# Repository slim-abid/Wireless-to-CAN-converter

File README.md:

# **Wireless to CAN converter**

Heracles is a qualified board for Automotive Applications.
The board was designed by KiCad.
It introduces the convertion between wireless connection (Bluetooth,BLE,WIFI) and CAN with the following features:

 - [ ] introduces a jtag debugging interface.
 
 - [ ] can be configured and managed by the integrated USB interface.
 
 - [ ] uses 3.8 to 38 V dc alimentation with very low drop down voltage
       values and very low power consumption .
 - [ ] ESP32­WROOM­32 running at 40Mhz to 160MHz.
 
 - [ ] A USB to UART converter.
 
 - [ ] USB type B port.
 
 - [ ] low-power co-processor that can be used instead of the CPU to
       save power while performing tasks that do not require much
       computing power, such as monitoring of peripherals.
       
 - [ ] Wireless connectivity: WI-FI (802.11 b/g/n ,802.11n up to 150
       Mbps), Bluetooth v4.2 and BLE.

## Schematic:

## PCB Routing

*All this capabilities are just in 6.65cmx5.35cm board.*

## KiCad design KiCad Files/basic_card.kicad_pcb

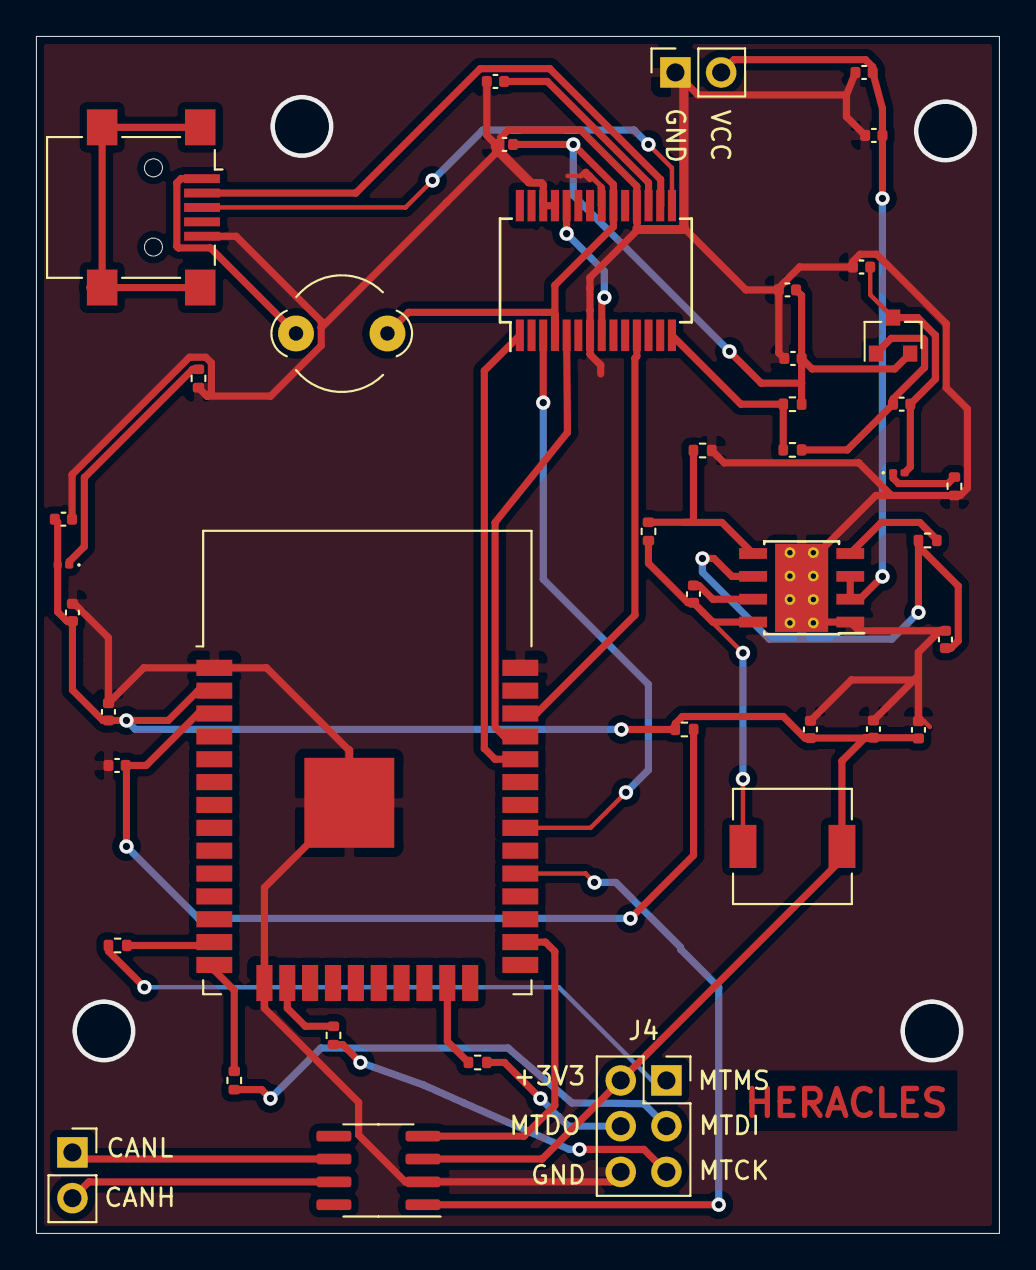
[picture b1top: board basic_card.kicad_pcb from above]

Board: 2 copper layers, 53.5 x 66.5 mm, 42 parts (0 on the bottom side), 35 nets.

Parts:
C1, C16: 10uF; C_0402_1005Metric
C2: 220nF; C_0402_1005Metric
C3: 10nF; C_0402_1005Metric
C4: C; C_0402_1005Metric
C5, C6, C8: 100nF; C_0402_1005Metric
C7: 4.7uF; C_0402_1005Metric
C9, C10, C11, C12: 22uF; C_0402_1005Metric
C13, C14, C17: 0.1uF; C_0402_1005Metric
C15: 1uF; C_0402_1005Metric
D1, D2: LED; LED_0201_0603Metric
FB1: Ferrite_Bead; LairdTech_28C0236-0JW-10
J1: USB_B_Mini; USB_Mini-B_Lumberg_2486_01_Horizontal
J2, J3: Screw_Terminal_01x02; PinSocket_1x02_P2.54mm_Vertical
J4: Conn_02x03_Odd_Even; PinSocket_2x03_P2.54mm_Vertical
L1: 6.8uH; L_6.3x6.3_H3
Q1: IRLML6402; SOT-23
R1: R; R_0402_1005Metric
R2: 100k; R_0402_1005Metric
R3: 43.2k; R_0402_1005Metric
R4, R9, R10: 1k; R_0402_1005Metric
R5, R6, R7, R11: 100; R_0402_1005Metric
R8, R12: 10k; R_0402_1005Metric
U1: SN65HVD232; SOIC-8_3.9x4.9mm_P1.27mm
U2: LMR33630ADDA; Texas_HSOP-8-1EP_3.9x4.9mm_P1.27mm_ThermalVias
U3: FT232RL; SSOP-28_5.3x10.2mm_P0.65mm
U4: ESP32-WROOM-32

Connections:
+3V3: C9.1, C10.1, C11.1, C12.1, C16.1, C17.1, D1.2, J4.2, L1.1, R12.1, U1.3, U4.2
+12V: C1.1, C2.1, J2.2, U2.2, U2.3
CAN_RXD: U1.4, U4.26
CAN_TXD: U1.1, U4.29
GND: C1.2, C2.2, C3.2, C4.2, C5.1, C6.1, C7.1, C9.2, C10.2, C11.2, C12.2, C14.2, C15.2, C16.2, C17.2, J1.5, J2.1, J4.6, R3.2, R4.2, R10.2, U1.2, U2.1, U2.9, U3.7, U3.18, U3.21, U3.25, U3.26, U4.1, U4.15, U4.38, U4.39
IO19: U3.3, U4.31
IO22: U3.11, U4.36
MTCK: R7.2, U4.16
MTDI: R6.2, U4.14
MTDO: R11.1, U4.23
MTMS: R5.2, U4.13
unnamed: C3.1, C6.2, C7.2, FB1.1, Q1.2, R8.1, U3.4, U3.20
unnamed: C4.1, R1.1, U2.6
unnamed: C5.2, U3.17
unnamed: C8.1, L1.2, R2.1, U2.8
unnamed: C8.2, U2.7
unnamed: C13.1, C14.1, D2.2, Q1.3
unnamed: C13.2, Q1.1, R9.1
unnamed: C15.1, R12.2, U4.3
unnamed: D1.1, R4.1
unnamed: D2.1, R10.1
unnamed: FB1.2, J1.1
unnamed: J1.2, U3.16
unnamed: J1.3, U3.15
unnamed: J3.1, U1.6
unnamed: J3.2, U1.7
unnamed: J4.1, R5.1
unnamed: J4.3, R6.1
unnamed: J4.4, R11.2
unnamed: J4.5, R7.1
unnamed: R2.2, R3.1, U2.5
unnamed: R8.2, R9.2, U3.14
PG: R1.2, U2.4
RX-ESP: U3.1, U4.34
TX-ESP: U3.5, U4.35

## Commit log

2021-04-21 first version of the board
